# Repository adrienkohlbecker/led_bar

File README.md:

# LED bar

## Board

## Schematic

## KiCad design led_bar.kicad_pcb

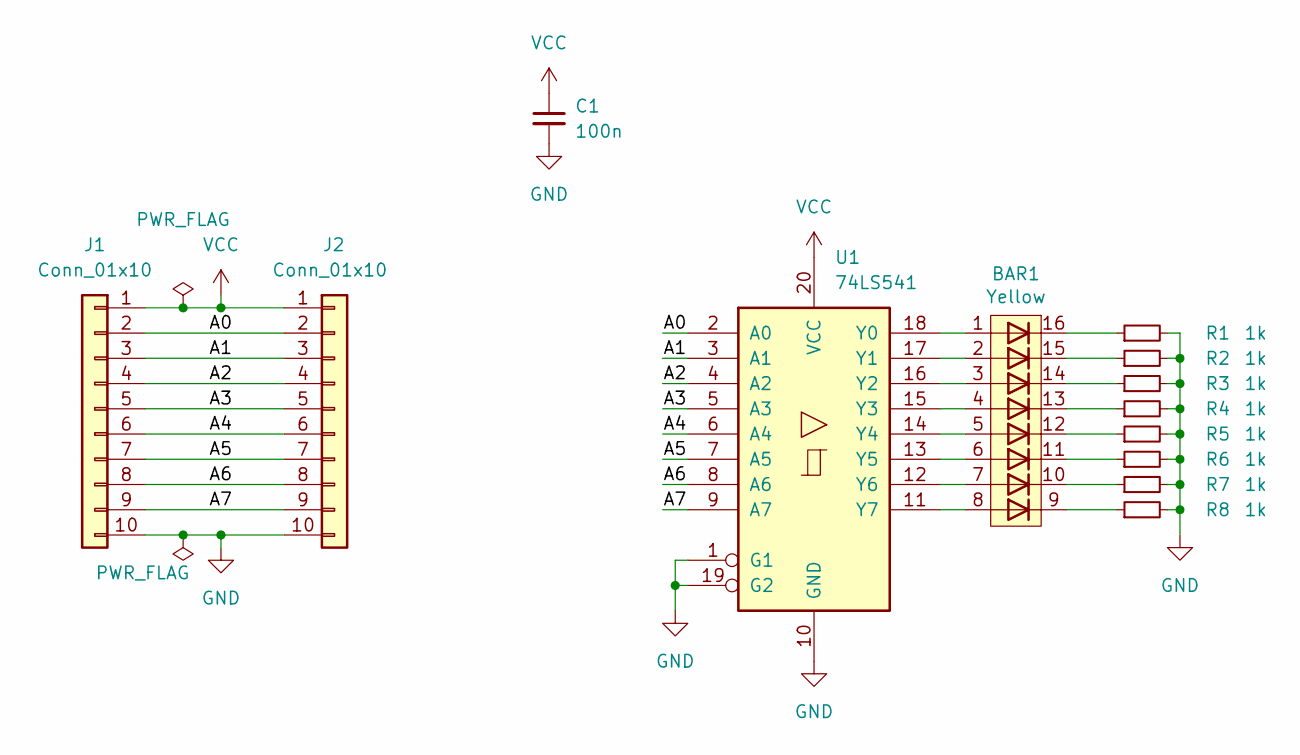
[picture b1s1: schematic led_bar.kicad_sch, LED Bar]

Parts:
BAR1: Yellow; DIP-16_W7.62mm
C1: 100n; C_Disc_D3.0mm_W1.6mm_P2.50mm
J1, J2: Conn_01x10; PinHeader_1x10_P2.54mm_Vertical
R1, R2, R3, R4, R5, R6, R7, R8: 1k; R_1206_3216Metric_Pad1.30x1.75mm_HandSolder
U1: 74LS541; DIP-20_W7.62mm

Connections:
/A0: J1.2, J2.2, U1.2 (A0)
/A1: J1.3, J2.3, U1.3 (A1)
/A2: J1.4, J2.4, U1.4 (A2)
/A3: J1.5, J2.5, U1.5 (A3)
/A4: J1.6, J2.6, U1.6 (A4)
/A5: J1.7, J2.7, U1.7 (A5)
/A6: J1.8, J2.8, U1.8 (A6)
/A7: J1.9, J2.9, U1.9 (A7)
GND: C1.2, J1.10, J2.10, R1.2, R2.2, R3.2, R4.2, R5.2, R6.2, R7.2, R8.2, U1.1 (G1), U1.10 (GND), U1.19 (G2)
unnamed: BAR1.1 (A), U1.18 (Y0)
unnamed: BAR1.2 (A), U1.17 (Y1)
unnamed: BAR1.3 (A), U1.16 (Y2)
unnamed: BAR1.4 (A), U1.15 (Y3)
unnamed: BAR1.5 (A), U1.14 (Y4)
unnamed: BAR1.6 (A), U1.13 (Y5)
unnamed: BAR1.7 (A), U1.12 (Y6)
unnamed: BAR1.8 (A), U1.11 (Y7)
unnamed: BAR1.9 (K), R8.1
unnamed: BAR1.10 (K), R7.1
unnamed: BAR1.11 (K), R6.1
unnamed: BAR1.12 (K), R5.1
unnamed: BAR1.13 (K), R4.1
unnamed: BAR1.14 (K), R3.1
unnamed: BAR1.15 (K), R2.1
unnamed: BAR1.16 (K), R1.1
VCC: C1.1, J1.1, J2.1, U1.20 (VCC)

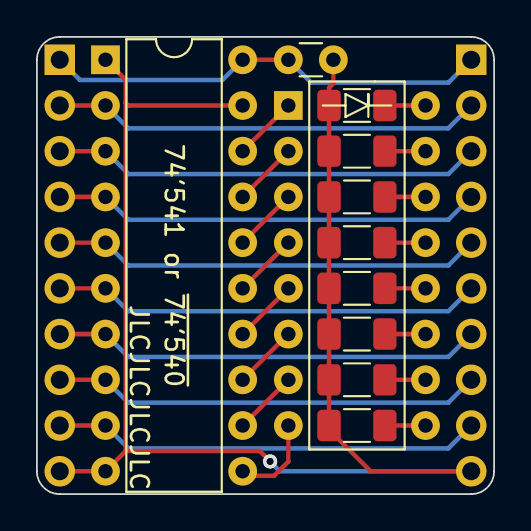
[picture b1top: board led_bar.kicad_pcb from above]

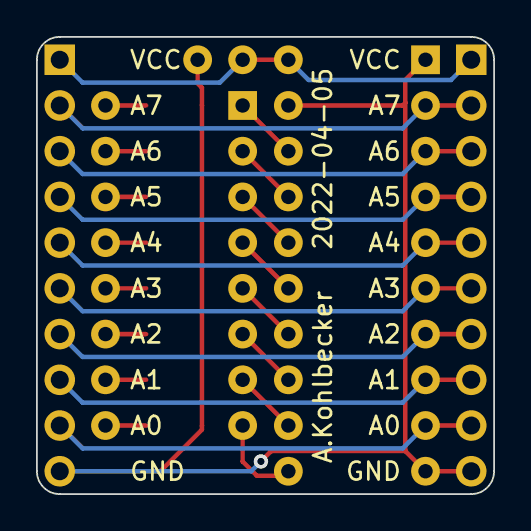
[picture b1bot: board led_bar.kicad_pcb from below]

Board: 2 copper layers, 25.4 x 25.4 mm, 13 parts (2 on the bottom side), 26 nets.
